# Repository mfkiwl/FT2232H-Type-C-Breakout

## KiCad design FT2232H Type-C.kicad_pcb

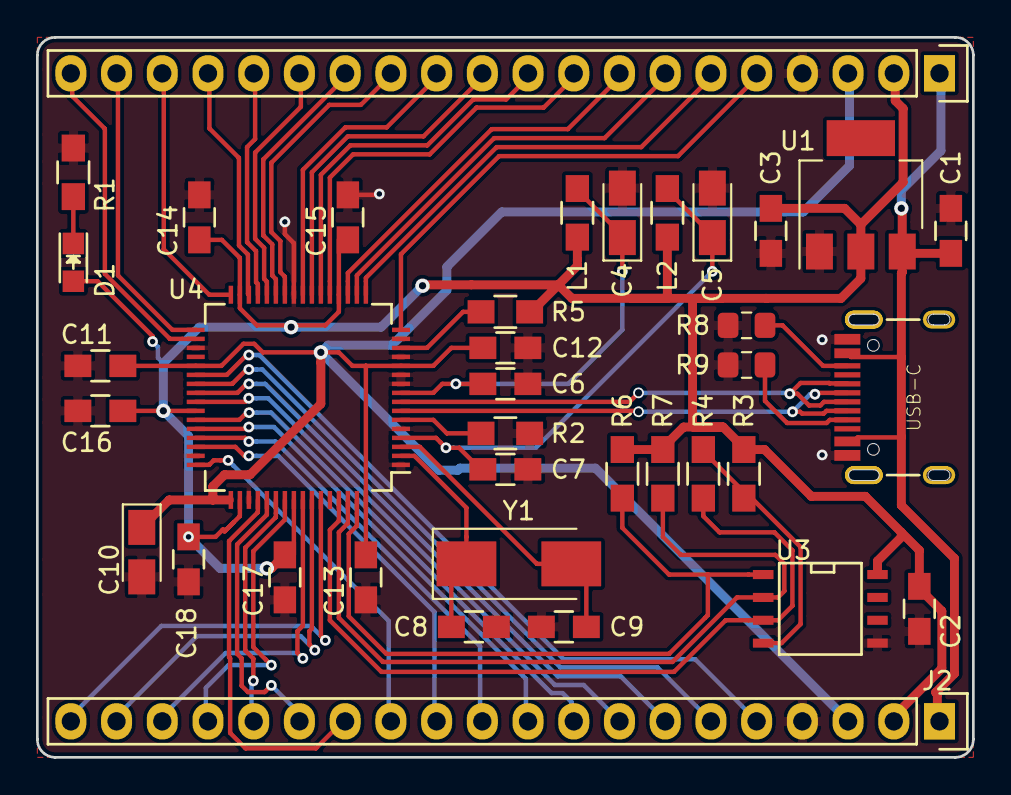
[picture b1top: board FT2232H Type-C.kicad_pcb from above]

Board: 2 copper layers, 52.0 x 40.0 mm, 37 parts (0 on the bottom side), 52 nets.

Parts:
C1, C2, C3, C6, C7, C11, C12, C13, C14, C15, C16, C17, C18: 0.1uF; C_0805_HandSoldering
C4, C5: 4.7uF; CP_Tantalum_Case-A_EIA-3216-18_Reflow
C8, C9: 27pF; C_0805_HandSoldering
C10: 3.3uF; CP_Tantalum_Case-A_EIA-3216-18_Reflow
D1: PWR; LED_0805
J1, J2: CONN_01X20; Socket_Strip_Straight_1x20
J3: USB_C16PIN; USB-C-COM-15111
L1, L2: L_Core_Ferrite; R_0805_HandSoldering
R1: 470R; R_0805_HandSoldering
R2: 12K 1%; R_0805_HandSoldering
R3, R6, R7: 10k; R_0805_HandSoldering
R4: 2.2k; R_0805_HandSoldering
R5: 10K; R_0805_HandSoldering
R8, R9: 5.1k; R_0805_2012Metric_Pad1.15x1.40mm_HandSolder
U1: LD1117S33TR; SOT-223
U3: 93CxxB; SOIC-8-N
U4: FT2232H; LQFP-64_10x10mm_Pitch0.5mm
Y1: 12Mhz; Crystal_SMD_0603-2pin_6.0x3.5mm_HandSoldering

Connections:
+1V8: C10.1, C11.1, C12.1, C13.1, J1.3, J2.3, U4.12, U4.37, U4.49, U4.64
+3V3: C2.1, C3.1, C14.1, C15.1, C16.1, C17.1, C18.1, D1.2, J1.2, J2.2, L1.1, L2.1, R3.1, R5.1, R6.1, R7.1, U1.2, U3.8, U4.20, U4.31, U4.42, U4.50, U4.56
+5V: C1.1, J1.1, J2.1, J3.VBUS1, J3.VBUS2, U1.3
/AC0: J1.13, U4.26
/AC1: J1.14, U4.27
/AC2: J1.15, U4.28
/AC3: J1.16, U4.29
/AC4: J1.17, U4.30
/AC5: J1.18, U4.32
/AC6: J1.19, U4.33
/AC7: J1.20, U4.34
/AD0: J1.5, U4.16
/AD1: J1.6, U4.17
/AD2: J1.7, U4.18
/AD3: J1.8, U4.19
/AD4: J1.9, U4.21
/AD5: J1.10, U4.22
/AD6: J1.11, U4.23
/AD7: J1.12, U4.24
/BC0: J2.13, U4.48
/BC1: J2.14, U4.52
/BC2: J2.15, U4.53
/BC3: J2.16, U4.54
/BC4: J2.17, U4.55
/BC5: J2.18, U4.57
/BC6: J2.19, U4.58
/BC7: J2.20, U4.59
/BD0: J2.5, U4.38
/BD1: J2.6, U4.39
/BD2: J2.7, U4.40
/BD3: J2.8, U4.41
/BD4: J2.9, U4.43
/BD5: J2.10, U4.44
/BD6: J2.11, U4.45
/BD7: J2.12, U4.46
/D+: J3.A6, J3.B6, U4.8
/D-: J3.A7, J3.B7, U4.7
GND: C1.2, C2.2, C3.2, C4.2, C5.2, C6.2, C7.2, C8.2, C9.2, C10.2, C11.2, C12.2, C13.2, C14.2, C15.2, C16.2, C17.2, C18.2, J1.4, J2.4, J3.GND, J3.GND2, R1.2, R2.2, R8.2, R9.2, U1.1, U3.5, U4.1, U4.5, U4.10, U4.11, U4.13, U4.15, U4.25, U4.35, U4.47, U4.51
unnamed: C4.1, C6.1, L1.2, U4.9
unnamed: C5.1, C7.1, L2.2, U4.4
unnamed: C8.1, U4.2, Y1.1
unnamed: C9.1, U4.3, Y1.2
unnamed: D1.1, R1.1
unnamed: J3.A5, R9.1
unnamed: J3.B5, R8.1
unnamed: J3.SHLD1, J3.SHLD2, J3.SHLD3, J3.SHLD4, J3.SHLD5, J3.SHLD6, J3.SHLD7, J3.SHLD8
unnamed: R2.1, U4.6
unnamed: R3.2, R4.2, U3.4
unnamed: R4.1, U3.3, U4.61
unnamed: R5.2, U4.14
unnamed: R6.2, U3.1, U4.63
unnamed: R7.2, U3.2, U4.62

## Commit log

2017-08-26 Remove bak file and add gitignore
2017-08-26 Ignore build folder
2017-08-26 Add silkscreen
2017-08-26 Add script to build fusion archive
2017-08-26 Fit J2 Silkscreen Position
2017-08-26 Couple of last minute fixes
2017-08-26 Fix some silkscreen placement
2017-10-27 Fix routing and add REGIN capacitor
2020-08-17 Update USB-C connector to check chinease version
2020-08-17 Update build file for new Kicad
2020-08-17 Update USB-C footprint
